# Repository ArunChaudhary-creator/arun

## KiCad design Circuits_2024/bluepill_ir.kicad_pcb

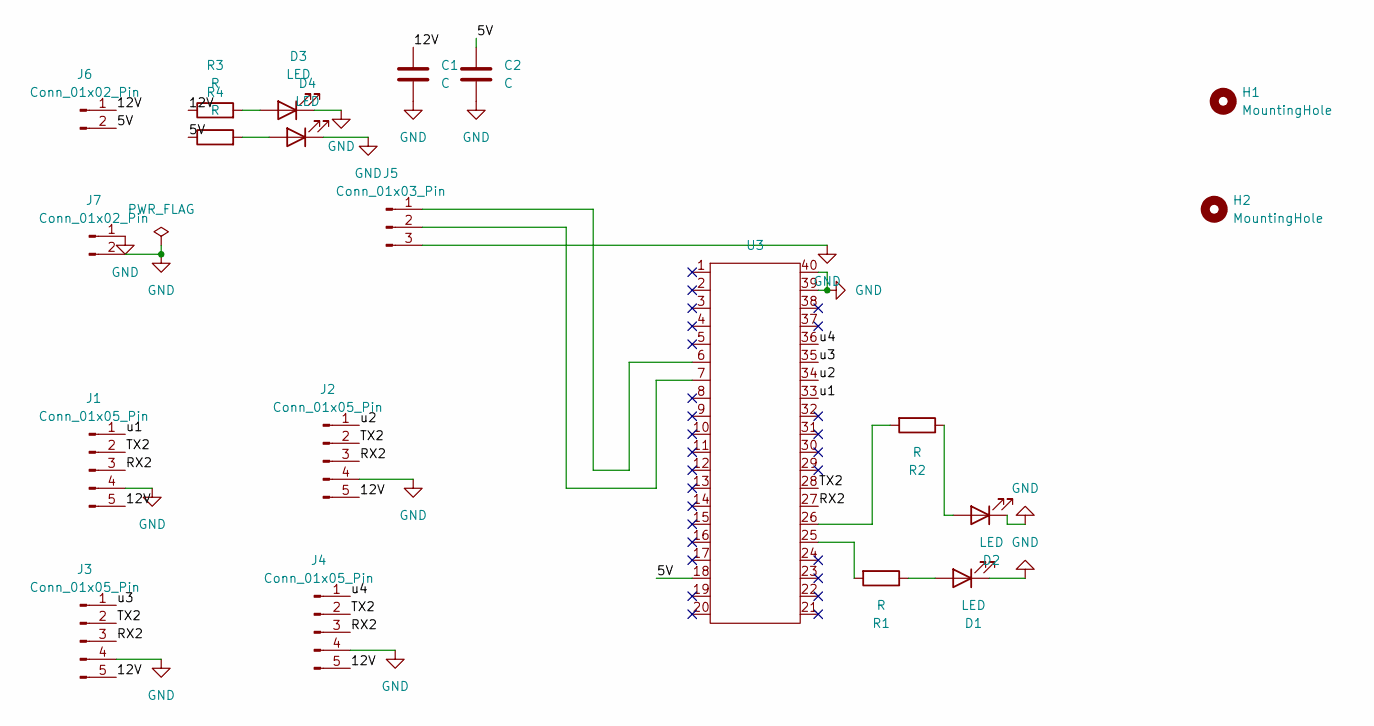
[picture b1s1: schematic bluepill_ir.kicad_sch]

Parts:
C1, C2: C; Capacitor_10uF
D1, D2, D3, D4: LED; LED_D3.0mm
H1, H2: MountingHole; MountingHole_3mm
J1, J2, J3, J4: Conn_01x05_Pin; jst_1x05
J5: Conn_01x03_Pin; jst_1x03
J6, J7: Conn_01x02_Pin; Connector_Bornier_2
R1, R2, R3, R4: R; Resistor_small
U3: bluepill

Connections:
/5V: C2.1, J6.2, R4.1, U3.18
/12V: C1.1, J1.5, J2.5, J3.5, J4.5, J6.1, R3.1
/RX2: J1.3, J2.3, J3.3, J4.3, U3.27
/TX2: J1.2, J2.2, J3.2, J4.2, U3.28
/u1: J1.1, U3.33
/u2: J2.1, U3.34
/u3: J3.1, U3.35
/u4: J4.1, U3.36
GND: C1.2, C2.2, D1.1 (K), D2.1 (K), D3.1 (K), D4.1 (K), J1.4, J2.4, J3.4, J4.4, J5.3, J7.1, J7.2, U3.39, U3.40
unnamed: D1.2 (A), R1.1
unnamed: D2.2 (A), R2.1
unnamed: D3.2 (A), R3.2
unnamed: D4.2 (A), R4.2
unnamed: J5.1, U3.6
unnamed: J5.2, U3.7
unnamed: R1.2, U3.25
unnamed: R2.2, U3.26

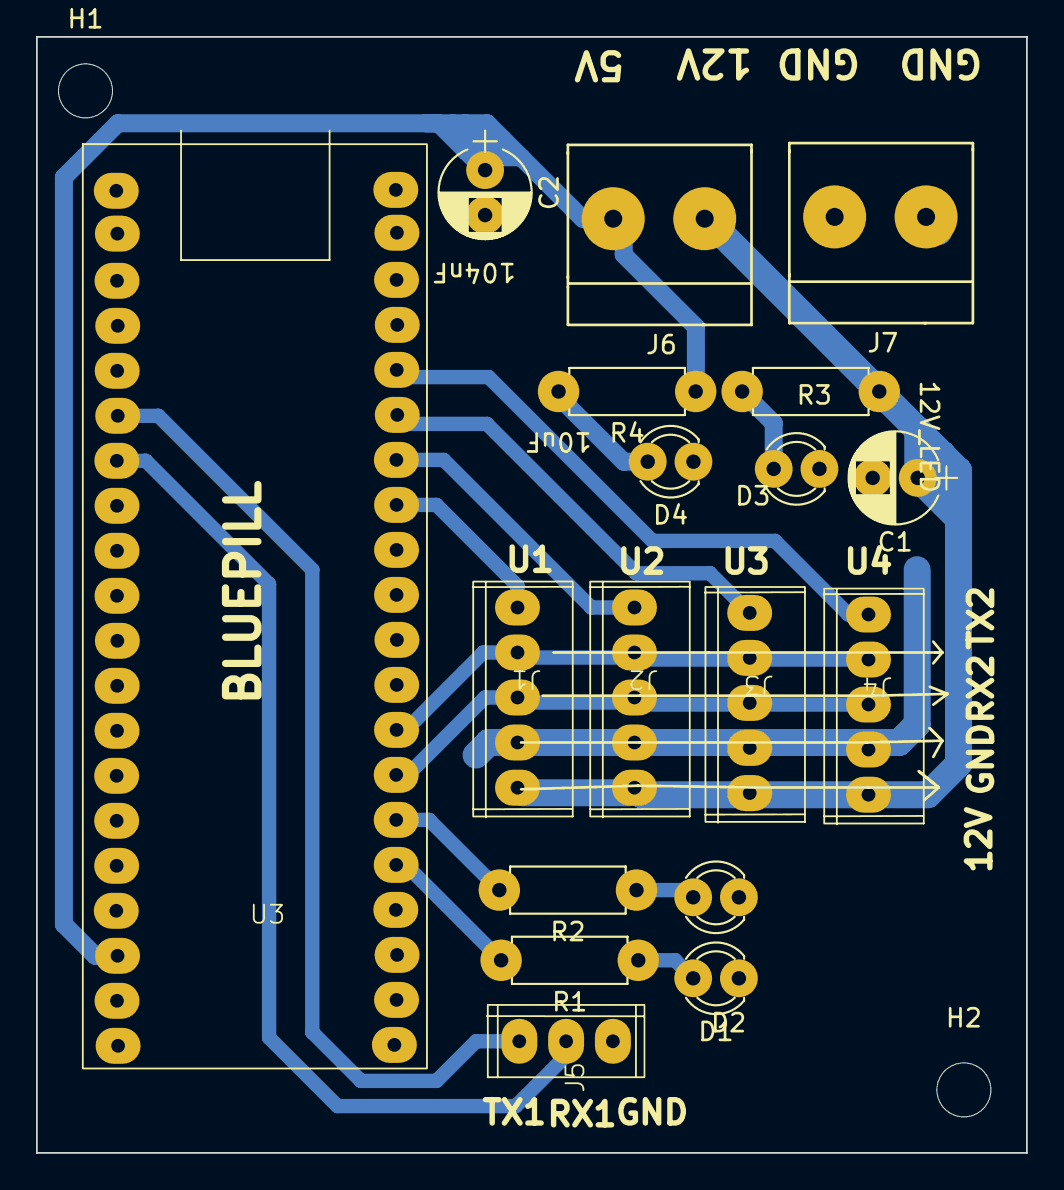
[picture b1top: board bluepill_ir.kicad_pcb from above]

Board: 2 copper layers, 55.0 x 62.0 mm, 20 parts (0 on the bottom side), 17 nets.

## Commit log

2024-04-23 test cpp file
2024-04-23 hello
2024-04-23 this is my test
2024-05-01 added bluepill_ir_new
2024-05-04 motor using arduino328P_U and blutooth..
2024-05-18 blue-pill_pinout circuit added
2024-05-18 circuit2024 added
